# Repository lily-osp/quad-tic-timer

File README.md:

# quad-tic-timer

A single ATtiny85 that puts out four synchronized tick channels from one knob. No 555s, no extra oscillators. You turn the pot and all four outputs speed up or slow down together, keeping their ratios exact.

It was built for a small robotics project that needed several timing references at once without adding boards or trimming four separate RC circuits.

## What it does

Four active-HIGH pulse outputs, 10 ms wide:

| Output | Pin | Nominal (pot centered) | Full CCW | Full CW |
|--------|-----|------------------------|----------|---------|
| o1 | PB0 | 1.00 s/tic | 0.20 s | 5.00 s |
| o2 | PB1 | 0.75 s/tic | 0.15 s | 3.75 s |
| o3 | PB2 | 0.50 s/tic | 0.10 s | 2.50 s |
| o4 | PB4 | 0.25 s/tic | 0.05 s | 1.25 s |

The pot sets one global scale factor `k` from 0.2 to 5.0. Center detent is 1.0x. The mapping is exponential, `k = 5^((adc-512)/512)`, so the slow end stays usable instead of bunching up the way a linear map would.

Timing is phase-accurate: each channel schedules its next edge as `next += period`, so error never accumulates. Ratios stay exact even while you turn the knob. Absolute accuracy follows the ATtiny85 internal oscillator, roughly 1% after factory calibration. That is an order of magnitude better than a 555 RC stage and fine for sequencing work.

## Wiring

```
ATtiny85 (SOIC-8/DIP-8, 8 MHz internal)
VCC -- 100nF -- GND (as close to the chip as possible)
PB3 -- pot wiper (10k 10-turn lin, ends to VCC/GND) + 10nF to GND
PB0 -- o1
PB1 -- o2
PB2 -- o3
PB4 -- o4
RST -- 10k to VCC (leave free for ISP)
```

Outputs drive LEDs through 330R or logic inputs directly. Total draw is a few mA plus loads.

Pot: 10k linear 10-turn precision type. Panel version is Bourns 3590S-1-103L with an H-22 turns-counting dial (5 turns from center to either end). If board space is tight, use the 25-turn trimmer Bourns 3296W-103 instead — same wiring, smaller, adjusted with a screwdriver. Either way center (5 turns from either stop) is the nominal 1.0x rate.

BOM: 1x ATtiny85, 1x 10k 10-turn pot, 1x 100nF, 1x 10nF, 1x 10k resistor. Nothing else.

## Build and flash

ATTinyCore, ATtiny85, 8 MHz internal, LTO enabled.

```bash
arduino-cli compile --fqbn ATTinyCore:avr:attinyx5:chip=85,clock=8internal quad-tic-timer.ino
avrdude -c usbasp -p t85 -U flash:w:quad-tic-timer.ino.hex:i -U lfuse:w:0xe2:m -U hfuse:w:0xdf:m -U efuse:w:0xff:m
```

Or open `quad-tic-timer.ino` in the Arduino IDE (sketchbook is at `microcontrollers/00_toolchain/arduino-ide`) and flash with USBasp / Arduino-as-ISP. Keep the reset pin enabled.

Check it with four LEDs first. Center the pot, o1 should blink once per second, o4 four times per second. Turn fully left and o1 runs at 5 Hz. Turn fully right and o1 takes 5 s per blink.

## Tuning

Two constants matter in `quad-tic-timer.ino`:

- `TIC_US` (10 ms) — shorten to 2–5 ms if the receiving logic is edge-sensitive and fast, lengthen to 20–50 ms for relays or optocouplers.
- The `> 2` deadband and 50 ms pot poll — tuned for a 10-turn pot (about 100 ADC steps per turn). Raise the deadband to 6–8 in a noisy supply, lower the poll to 20 ms if you want a snappier knob.

Pot reads are averaged over 16 samples and referenced to VCC, so the reading is ratiometric and supply drift largely cancels out. One ADC step is about 0.3% rate change at mid-scale, roughly a third of a turn feel on a 10-turn pot.

## Where it fits

- Robot gait and sequencer clocks: one channel steps the main loop, the faster channels drive leg phases, sensor polls, or status blinks from the same tempo.
- Sensor scheduler: poll slow sensors on o1/o2, fast IMU or encoder sampling on o3/o4, all slowing together in low-power mode.
- Servo/stepper test bench: sweep the whole timing tree with one hand while watching mechanics respond.
- Automation and stage props: trigger solenoids, pumps, or lights at related intervals without a full PLC.
- Camera trap / timelapse: o1 fires the shutter, o4 wakes the focus/metering chain just before.
- Music and kinetic art: clock dividers for drum triggers, solenoids, or LED chases.

Any place that currently uses two to four 555s for related rates is a candidate. This replaces them with one 8-pin chip and holds ratio over temperature far better than RC timing.

## Limits

- Not a reference clock. The internal oscillator drifts about 1–2% with voltage and temperature. Ratios are exact, absolute rate is not.
- Shortest period is 50 ms on o4 at full CCW. The 10 ms pulse is then 20% duty, which is fine for logic but too wide for some edge counters. Adjust `TIC_US` if that matters.
- ADC noise on a long wiper wire can make the tempo wander at the extremes. Keep the wiper lead short and keep the 10nF cap.

If you later need crystal accuracy, port the sketch unchanged to an ATmega328P Nano clone or STM32 Blue Pill and set the same four pins. For lab-grade absolute rate, feed a DS3231 1 Hz TCXO into a spare input and discipline `k` against it.

## Files

```
quad-tic-timer/
  quad-tic-timer.ino  firmware, ATtiny85, single sketch, no dependencies
  README.md           this file
  .gitignore          Arduino/AVR/PlatformIO ignores
  pcb/                production 30x30mm KiCad 9 PCB & JLCPCB manufacturing package
    quad-tic-timer.kicad_pcb
    quad-tic-timer.kicad_sch
    quad-tic-timer-drc.rpt
    quad-tic-timer-erc.rpt
    jlcpcb_production/  Gerbers, BOM, CPL, 3D renders
```

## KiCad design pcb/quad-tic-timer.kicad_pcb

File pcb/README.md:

# Quad-Tic-Timer: ATtiny85 Synchronized Robotic Pulse Generator PCB

A 30x30mm 2-layer KiCad 9 development board for the **Quad-Tic-Timer** firmware. Driven by an **Atmel ATtiny85-20SU**, it provides four synchronized phase-accurate pulse outputs scaled exponentially by a single precision 10-turn control pot.

Designed and verified using the **pcb** skill with full **KiCad 9** headless tooling and production-ready **JLCPCB** fabrication deliverables.

---

## 📌 3D Render Previews

| Top Side (Components & Telemetry) | Bottom Side (Ground Plane & Labeling) |
| :---: | :---: |
|  |  |

---

## ⚡ Hardware Architecture & Features

- **Microcontroller**: Microchip / Atmel **ATtiny85-20SU** (SOIC-8, 8 MHz internal calibrated RC oscillator).
- **Quad Synchronized Pulse Outputs**:
  - `O1` (PB0 / Pin 5): 1.00 s/tic nominal (0.20 s – 5.00 s range)
  - `O2` (PB1 / Pin 6): 0.75 s/tic nominal (0.15 s – 3.75 s range)
  - `O3` (PB2 / Pin 7): 0.50 s/tic nominal (0.10 s – 2.50 s range)
  - `O4` (PB4 / Pin 3): 0.25 s/tic nominal (0.05 s – 1.25 s range)
- **Dual Potentiometer Sourcing**:
  - **Onboard Trimmer**: Bourns 3296W vertical 10k 25-turn potentiometer (`RV1`).
  - **External Pot Header**: 1x03 2.54mm pin header (`JEXT`) for panel-mount 10-turn pots (Bourns 3590S).
  - **Source Select Jumper**: 1x03 2.54mm header (`JP1`). Jumper pins 1-2 for onboard trimmer, 2-3 for external pot.
- **Power & Conditioning**:
  - `C1` (100nF 0805): Dedicated VCC decoupling placed within 2 mm of U1 pin 8.
  - `C2` (10nF 0805): Low-pass noise filter on ADC3 wiper input (U1 pin 2).
  - `R5` (10k 0805): Pull-up on RESET (pin 1) keeping reset line high while leaving it ISP-programmable.
  - `JPWR` (1x02): 5V DC input.
- **Visual Status Telemetry**:
  - Four independent 0805 LEDs (`D1`–`D4`) driven through 1kΩ ballast resistors (`R1`–`R4`) indicating pulse ticks on each channel.
- **Output Interface**:
  - `JOUT` (1x06 2.54mm header): Exposes `O1`, `O2`, `O3`, `O4`, `VCC`, and `GND`.
- **Board Specifications**:
  - Form factor: **30.0 mm x 30.0 mm** with 2.0 mm corner chamfers.
  - Layer stack: 2-layer (1.6 mm FR4, 1 oz Cu, HASL lead-free).
  - Bottom layer: Continuous low-impedance ground plane (`B.Cu`).
  - Free prototype rule compliant (well within JLCPCB 100x100mm bounds).

---

## 🗂️ Project Deliverables (Zero Bloat)

```text
quad-tic-timer/pcb/
├── README.md                      # Comprehensive technical hardware documentation
├── fp-info-cache                  # KiCad footprint library cache
├── quad-tic-timer.kicad_pro       # KiCad 9 project file
├── quad-tic-timer.kicad_prl       # KiCad 9 local settings file
├── quad-tic-timer.kicad_sch       # KiCad 9 complete schematic with embedded symbols
├── quad-tic-timer.kicad_pcb       # KiCad 9 fully routed board (0 DRC, 0 unconnected)
├── quad-tic-timer-drc.rpt         # Official KiCad DRC report (0 errors, 0 warnings)
├── quad-tic-timer-erc.rpt         # Official KiCad ERC report (0 errors, 0 warnings)
└── jlcpcb_production/             # Turn-key manufacturing archive
    ├── quad-tic-timer_gerber_jlcpcb.zip  # RS-274X Gerbers + Excellon NC drills
    ├── quad-tic-timer_bom_jlcpcb.csv     # Bill of Materials formatted for JLCPCB
    ├── quad-tic-timer_cpl_jlcpcb.csv     # Pick-and-place centroid coordinate file
    ├── quad-tic-timer_render_top.png     # Photorealistic 3D top render
    └── quad-tic-timer_render_bottom.png  # Photorealistic 3D bottom render
```

---

## ⚡ Bill of Materials (BOM)

| Designator | Description | Footprint | LCSC Part # | Qty |
| :--- | :--- | :--- | :--- | :--- |
| **U1** | ATtiny85-20SU 8-bit AVR Microcontroller | SOIC-8_3.9x4.9mm_P1.27mm | C44533 | 1 |
| **RV1** | 10k Precision Multi-turn Trimpot | Bourns_3296W_Vertical | C180126 | 1 |
| **C1** | 100nF 50V Ceramic Capacitor | C_0805_2012Metric | C49678 | 1 |
| **C2** | 10nF 50V Ceramic Capacitor | C_0805_2012Metric | C1710 | 1 |
| **R5** | 10kΩ 1% 1/8W Pullup Resistor | R_0805_2012Metric | C17414 | 1 |
| **R1–R4** | 1kΩ 1% 1/8W LED Current-Limiters | R_0805_2012Metric | C17513 | 4 |
| **D1–D4** | Green LED Indicators | LED_0805_2012Metric | C2297 | 4 |
| **JPWR** | 1x02 2.54mm Pin Header (Power In) | PinHeader_1x02_P2.54mm_Vertical | C2241 | 1 |
| **JP1** | 1x03 2.54mm Pin Header (Pot Select) | PinHeader_1x03_P2.54mm_Vertical | C2242 | 1 |
| **JEXT** | 1x03 2.54mm Pin Header (Ext Pot) | PinHeader_1x03_P2.54mm_Vertical | C2242 | 1 |
| **JOUT** | 1x06 2.54mm Pin Header (Signal Out) | PinHeader_1x06_P2.54mm_Vertical | C2245 | 1 |

---

## 🔍 Verification & Quality Assurance

1. **Pre-flight Placement Validation**:
   - Courtyard overlaps: **0 collisions**
   - Minimum edge clearance: **> 0.5 mm** across all footprints
2. **Electrical Rules Check (ERC)**:
   - `quad-tic-timer-erc.rpt`: **0 errors, 0 warnings**
   - All 47 electrical nodes matched 1:1 with PCB netlist
3. **Design Rules Check (DRC)**:
   - `quad-tic-timer-drc.rpt`: **0 errors, 0 warnings, 0 unconnected items**
   - Minimum track width: 0.25 mm (well above 0.15 mm JLCPCB limit)
   - Minimum track clearance: 0.20 mm
   - Minimum via drill/diameter: 0.30 mm / 0.60 mm
4. **Manufacturing Package Integrity**:
   - Drill Census: 27 drilled holes (2 files, PTH + NPTH)
   - Board outline verified on `Edge_Cuts` (`.gm1`)
   - Gerbers tested and packaged into `quad-tic-timer_gerber_jlcpcb.zip` ready for one-click upload.

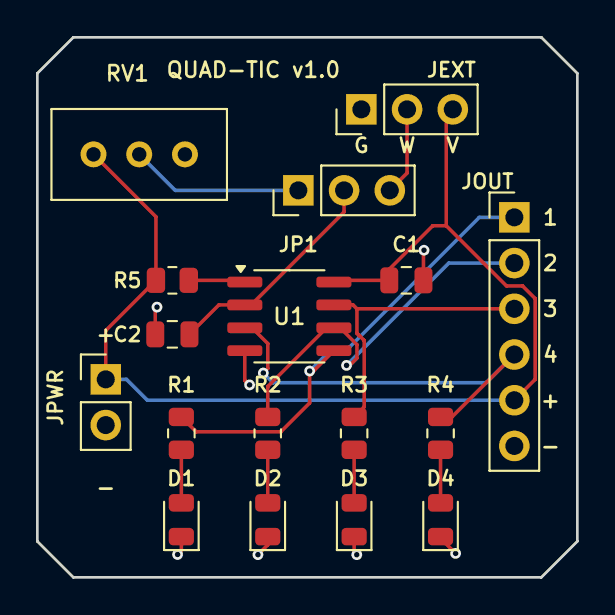
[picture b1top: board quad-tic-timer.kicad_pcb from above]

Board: 2 copper layers, 30.0 x 30.0 mm, 17 parts (0 on the bottom side), 14 nets.

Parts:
C1: 100n; C_0805_2012Metric
C2: 10n; C_0805_2012Metric
D1: O1; LED_0805_2012Metric
D2: O2; LED_0805_2012Metric
D3: O3; LED_0805_2012Metric
D4: O4; LED_0805_2012Metric
JEXT: EXT-POT; PinHeader_1x03_P2.54mm_Vertical
JOUT: OUT; PinHeader_1x06_P2.54mm_Vertical
JP1: POT-SEL; PinHeader_1x03_P2.54mm_Vertical
JPWR: PWR; PinHeader_1x02_P2.54mm_Vertical
R1, R2, R3, R4: 1k; R_0805_2012Metric
R5: 10k; R_0805_2012Metric
RV1: 10k; Potentiometer_Bourns_3296W_Vertical
U1: ATtiny85; SOIC-8_3.9x4.9mm_P1.27mm

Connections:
GND: C1.2, C2.1, D1.1, D2.1, D3.1, D4.1, JEXT.1, JOUT.6, JPWR.2, RV1.1, U1.4
N_EXTW: JEXT.2, JP1.3
N_LED1: D1.2, R1.2
N_LED2: D2.2, R2.2
N_LED3: D3.2, R3.2
N_LED4: D4.2, R4.2
N_POT: C2.2, JP1.2, U1.2
N_RST: R5.2, U1.1
N_RVW: JP1.1, RV1.2
O1: JOUT.1, R1.1, U1.5
O2: JOUT.2, R2.1, U1.6
O3: JOUT.3, R3.1, U1.7
O4: JOUT.4, R4.1, U1.3
VCC: C1.1, JEXT.3, JOUT.5, JPWR.1, R5.1, RV1.3, U1.8

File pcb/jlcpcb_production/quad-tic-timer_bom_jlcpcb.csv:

"Refs","Value","Footprint","Qty","DNP"
"C1","100n","Capacitor_SMD:C_0805_2012Metric","1",""
"C2","10n","Capacitor_SMD:C_0805_2012Metric","1",""
"D1","LED-O1","LED_SMD:LED_0805_2012Metric","1",""
"D2","LED-O2","LED_SMD:LED_0805_2012Metric","1",""
"D3","LED-O3","LED_SMD:LED_0805_2012Metric","1",""
"D4","LED-O4","LED_SMD:LED_0805_2012Metric","1",""
"JEXT","EXT-POT","Connector_PinHeader_2.54mm:PinHeader_1x03_P2.54mm_Vertical","1",""
"JOUT","OUT","Connector_PinHeader_2.54mm:PinHeader_1x06_P2.54mm_Vertical","1",""
"JP1","POT-SEL","Connector_PinHeader_2.54mm:PinHeader_1x03_P2.54mm_Vertical","1",""
"JPWR","PWR","Connector_PinHeader_2.54mm:PinHeader_1x02_P2.54mm_Vertical","1",""
"R1","1k","Resistor_SMD:R_0805_2012Metric","1",""
"R2","1k","Resistor_SMD:R_0805_2012Metric","1",""
"R3","1k","Resistor_SMD:R_0805_2012Metric","1",""
"R4","1k","Resistor_SMD:R_0805_2012Metric","1",""
"R5","10k","Resistor_SMD:R_0805_2012Metric","1",""
"RV1","10k","Potentiometer_THT:Potentiometer_Bourns_3296W_Vertical","1",""
"U1","ATtiny85","Package_SO:SOIC-8_3.9x4.9mm_P1.27mm","1",""
